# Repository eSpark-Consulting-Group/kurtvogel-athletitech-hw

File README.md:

# Athletitech Product Hardware Development and Enhancements
#### Client Name: Kurt Vogel

## Project Requirements
Outlined in Tickets

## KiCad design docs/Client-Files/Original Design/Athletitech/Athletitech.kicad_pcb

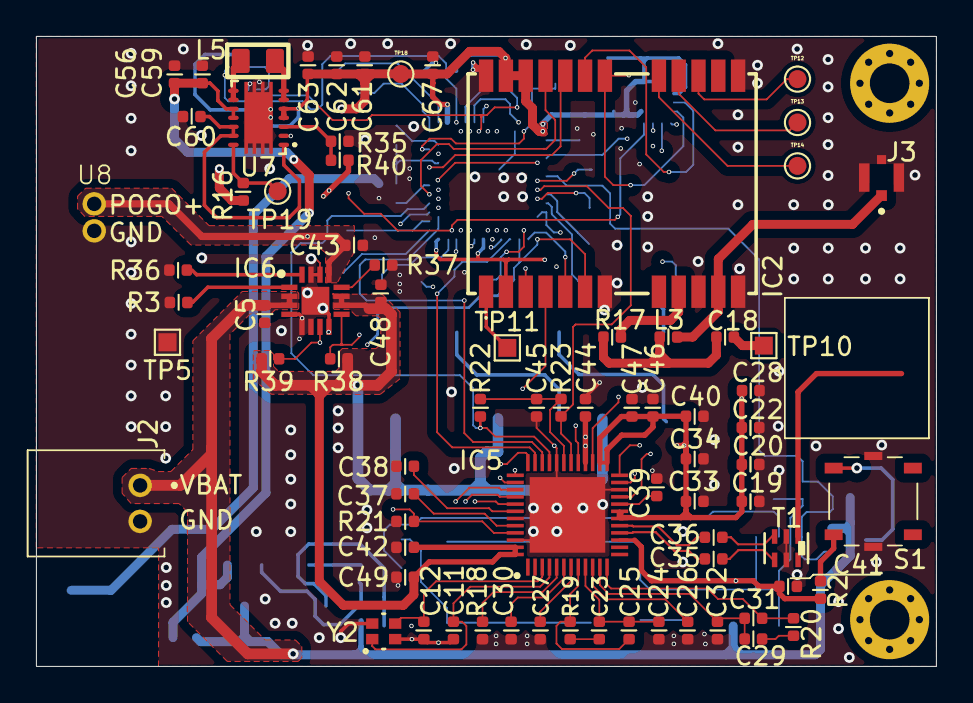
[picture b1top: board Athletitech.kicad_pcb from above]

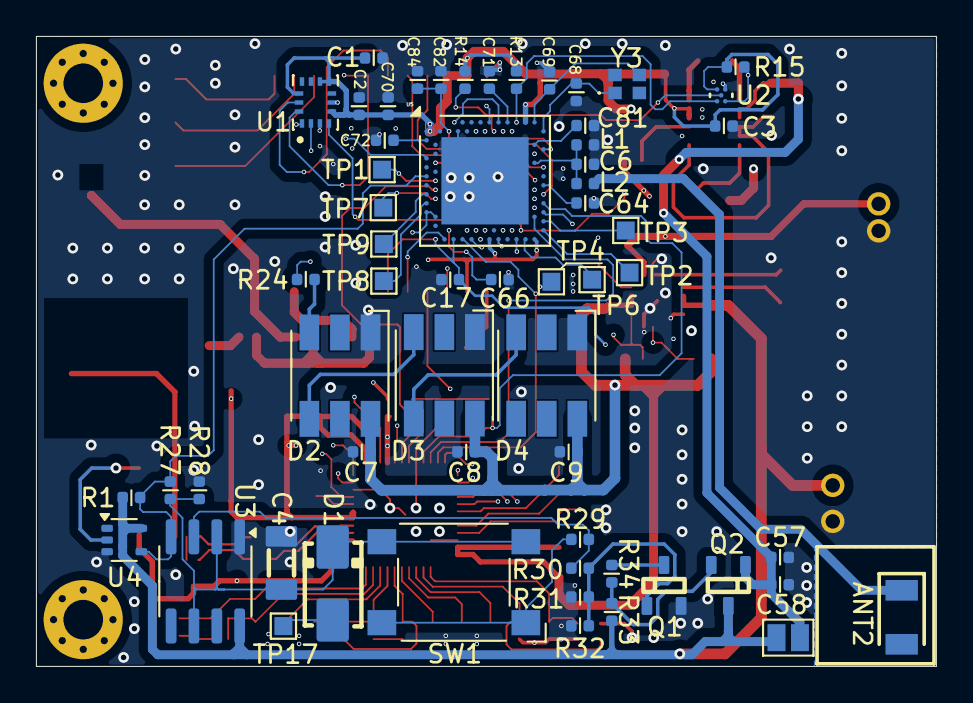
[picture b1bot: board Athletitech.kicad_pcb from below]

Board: 4 copper layers, 50.0 x 35.0 mm, 139 parts (60 on the bottom side), 102 nets.

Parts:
ANT2: 2450AT18B100E; ANTC3216X140N
C1, C2, C3, C27, C30, C43, C60, C72: 100nF; C_0402_1005Metric
C4: 1uF; C_1206
C5, C48: 470nF; C_0402_1005Metric
C6: 1.2pF; C_0402_1005Metric
C7, C8, C9: 0.1uF; C_0402_1005Metric
C11, C12: 10pF; C_0402_1005Metric
C17, C66: 4.7uF; C_0402_1005Metric
C18, C20, C24, C26, C32, C33, C37, C38, C39, C42, C44, C45, C46, C47, C49, C67: 100nf; C_0402_1005Metric
C19: 47uf; C_0402_1005Metric
C22, C34: 10pf; C_0402_1005Metric
C23: 27pf; C_0402_1005Metric
C25: 1P2; C_0402_1005Metric
C28, C40: 330pf; C_0402_1005Metric
C29: 820pf; C_0402_1005Metric
C31: 18pf; C_0402_1005Metric
C35, C36, C68, C69: 12pf; C_0402_1005Metric
C41: 10000pf; C_0402_1005Metric
C56, C59: 10uF; C_0402_1005Metric
C57: 10uF/25V; C_0402_1005Metric
C58: 0.1uF/25V; C_0402_1005Metric
C61, C62, C63: 22uf; C_0402_1005Metric
C64: 820pF; C_0402_1005Metric
C70, C84: 1uF; C_0402_1005Metric
C71, C82: 5pF; C_0402_1005Metric
C81: 100pf; C_0402_1005Metric
D1: B120-E3/61t; D_SMA
D2, D3, D4: SMD-LX5050RGB-TR; LED_RGB_5050-6
H1, H2: MountingHole_Pad; MountingHole_2.2mm_M2_Pad_Via
IC2: NEO-M9N-00B; NEOM9N00B
IC5: DW1000-I-TR13; QFN40P600X600X90-49N-D
IC6: BQ24075RGTT; QFN50P300X300X80-17N-D
J2: S2B-PH-K-S; S2BPHKS
J3: CONMHF4-SMD-G-T; LINX_CONMHF4-SMD-G-T
JP1: Jumper_2_Open; SolderJumper-2_P1.3mm_Open_Pad1.0x1.5mm
L1: 2.7nH; L_0402_1005Metric
L2: 3.3nH; L_0402_1005Metric
L3: 27nH; C_0402_1005Metric
L5: 1.5uH; L_0805
Q1: FDN337N; SOT23-3
Q2: NTR4101PT1G; SOT23-3
R1: 1k; C_0402_1005Metric
R2: 1K; C_0402_1005Metric
R3: 10kΩ; C_0402_1005Metric
R13, R14: 4k7; C_0402_1005Metric
R15: 1k2; C_0402_1005Metric
R16, R40: 1M; C_0402_1005Metric
R17: 10Ω; C_0402_1005Metric
R18: 11K; C_0402_1005Metric
R19: 16K; C_0402_1005Metric
R20: 270; C_0402_1005Metric
R21, R29, R32, R33: 100K; C_0402_1005Metric
R22, R23, R27, R28, R34: 10K; C_0402_1005Metric
R24: 330R; C_0402_1005Metric
R30: 220; C_0402_1005Metric
R31: DNP; C_0402_1005Metric
R35: 180K; C_0402_1005Metric
R36: 1.13kΩ; C_0402_1005Metric
R37: 1.18kΩ; C_0402_1005Metric
R38, R39: 100kΩ; C_0402_1005Metric
S1: EVQ-PT5A15; EVQPT5A15
SG-WFWLB1: TLV493DA2BWXTMA1; SG-WFWLB-5-2
SW1: SW_Omron_B3FS; SW_SPST_Omron_B3FS-100xP
T1: HHM1595A1; HHM-6_2P0X1P25
TP1, TP2, TP3, TP4, TP5, TP6, TP7, TP8, TP9, TP10, TP11, TP17: TestPoint; TestPoint_Pad_1.0x1.0mm
TP12, TP13, TP14, TP18: TestPoint; TestPoint_Pad_D1.0mm
TP19: Power Good; TestPoint_Pad_D1.0mm
U1: ICM-45686; IC_ICM-45686
U3: TLC555IDR; SOIC-8_3.9x4.9mm_P1.27mm
U4: 74AUP1G06, DNP; SOT-353_SC-70-5
U5: nRF52840; Nordic_AQFN-73-1EP_7x7mm_P0.5mm
U7: TPS63020; QFN14-3X4MM
U8: Mill_Max_854-22-002-20-041101
Y2: 8Y38472012; 8Y384_TXC
Y3: XRCGB32M000F1S1DR0; XRCGB

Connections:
+3.3V: C1.1, C2.1, C3.1, C7.1, C8.1, C9.1, C19.2, C20.1, C22.2, C28.2, C33.1, C34.2, C40.2, C41.2, C42.1, C44.1, C46.1, C47.1, C48.1, C49.1, C61.1, C62.1, C63.1, C67.1, C70.1, D2.6 (VDD), D3.6 (VDD), D4.6 (VDD), IC2.2 (D_SEL), IC2.22 (V_BCKP), IC2.23 (VCC), IC5.15 (VDDLNA), IC5.18 (VDDPA1), IC5.19 (VDDPA2), IC5.25 (VDDAON), IC5.26 (VDDLDOD), IC5.28 (VDDIOA), IC5.47 (VDDBATT), IC5.48 (VDDLDOA), IC6.10 (OUT_1), IC6.11 (OUT_2), R2.1, R13.1, R14.1, R15.1, R16.1, R38.1, R39.1, R40.2, SG-WFWLB1.C3 (VDD), TP18.1, U1.5 (VDDIO), U1.8 (VDD), U1.9 (INT2/FSYNC/CLKIN), U1.12 (AP_CS), U5.A22 (VDD), U5.AD14 (VDD), U5.AD23 (VDD), U5.B1 (VDD), U5.W1 (VDD), U5.Y2 (VDDH), U7.4 (VOUT), U7.5 (VOUT_2)
/BAT_OUT: C56.2, C57.1, C58.1, C59.2, JP1.2 (B), Q2.1 (D), U7.10 (VIN), U7.11 (VIN_2)
/Charger - BQ24075/BAT_STATUS_READ: IC6.7 (~PGOOD), R39.2, U5.H2 (P0.27)
/Charger - BQ24075/BAT_nRF: IC6.9 (~CHG), R38.2, U5.V23 (P1.03)
/GNSS - NEO-M9N-00B/EXTINT0: IC2.4 (EXTINT), U5.AC11 (P0.16)
/GNSS - NEO-M9N-00B/PPS: IC2.3 (TIMEPULSE), U5.B13 (AIN1/P0.03)
/GNSS - NEO-M9N-00B/RXD_SPIMOSI: IC2.21 (RXD_/_SPI_MOSI), U5.R24 (P1.06)
/GNSS - NEO-M9N-00B/TXD_SPIMISO: IC2.20 (TXD_/_SPI_MISO), U5.J24 (NFC2/P0.10)
/GNSS - NEO-M9N-00B/USB_D-: IC2.5 (USB_DM), U5.AD4 (D-)
/IMU - ICM-45686/INT1/INT: R15.2, SG-WFWLB1.A1 (/INT), U1.4 (INT1/INT), U5.AC21 (P0.25)
/IMU - ICM-45686/MAS_CLK: U1.3 (RESV/AUX1_SCLK/MAS_CLK), U5.G1 (P0.26)
/IMU - ICM-45686/MAS_DA: U1.2 (RESV/AUX1_SDIO/AUX1_SDI/MAS_DA), U5.A14 (P1.15)
/IMU - ICM-45686/SDO: U1.1 (AP_SDO/AP_AD0), U5.B17 (P1.12)
/MCU - NRF52840-CKAA-R7/DEC1: C72.1, U5.C1 (DEC1)
/MCU - NRF52840-CKAA-R7/DEC3: C81.2, U5.D23 (DEC3)
/MCU - NRF52840-CKAA-R7/DEC4_6: C82.2, C84.2, U5.B5 (DEC4), U5.E24 (DEC6)
/MCU - NRF52840-CKAA-R7/EXTON: IC5.21 (EXTON), U5.AC19 (P0.23)
/MCU - NRF52840-CKAA-R7/GPIO0: IC5.38 (GPIO0/RXOKLED), U5.B19 (P1.11)
/MCU - NRF52840-CKAA-R7/GPIO1: IC5.37 (GPIO1/SFDLED), U5.A16 (P1.13)
/MCU - NRF52840-CKAA-R7/GPIO2: IC5.36 (GPIO2/RXLED), U5.AD10 (P0.15)
/MCU - NRF52840-CKAA-R7/GPIO3: IC5.35 (GPIO3/TXLED), U5.AD8 (P0.13)
/MCU - NRF52840-CKAA-R7/GPIO4: IC5.34 (GPIO4/EXTPA), U5.Y23 (P1.01)
/MCU - NRF52840-CKAA-R7/IRQ: IC5.45 (IRQ/GPIO8), R21.1, U5.P23 (P1.07)
/MCU - NRF52840-CKAA-R7/LED_DIN: R24.1, U5.B11 (AIN4/P0.28)
/MCU - NRF52840-CKAA-R7/P0.07_TRACECLK: TP1.1, U5.M2 (TRACECLK/P0.07)
/MCU - NRF52840-CKAA-R7/P0.11_TRACEDATA2: TP7.1, U5.T2 (TRACEDATA2/P0.11)
/MCU - NRF52840-CKAA-R7/P0.12_TRACEDATA1: TP8.1, U5.U1 (TRACEDATA1/P0.12)
/MCU - NRF52840-CKAA-R7/P1.00_TRACEDATA0: TP6.1, U5.AD22 (TRACEDATA0/P1.00)
/MCU - NRF52840-CKAA-R7/P1.09_TRACEDATA3: TP9.1, U5.R1 (TRACEDATA3/P1.09)
/MCU - NRF52840-CKAA-R7/RESET: TP4.1, U5.AC13 (P0.18/~RESET)
/MCU - NRF52840-CKAA-R7/RSTn: IC5.27 (RSTN), U5.T23 (P1.05)
/MCU - NRF52840-CKAA-R7/SPICLK: IC5.41 (SPICLK), U5.AC9 (P0.14)
/MCU - NRF52840-CKAA-R7/SPICSN: IC5.24 (SPICSN), U5.AC17 (P0.21)
/MCU - NRF52840-CKAA-R7/SPIMISO: IC5.40 (SPIMISO), U5.AD12 (P0.17)
/MCU - NRF52840-CKAA-R7/SPIMOSI: IC5.39 (SPIMOSI), U5.AD16 (P0.20)
/MCU - NRF52840-CKAA-R7/SWDCLK: TP3.1, U5.AA24 (SWDCLK)
/MCU - NRF52840-CKAA-R7/SWDIO: TP2.1, U5.AC24 (SWDIO)
/MCU - NRF52840-CKAA-R7/SYNC: IC5.29 (SYNC/GPIO7), U5.W24 (P1.02)
/MCU - NRF52840-CKAA-R7/WAKEUP: IC5.23 (WAKEUP), U5.AD20 (P0.24)
/MCU - NRF52840-CKAA-R7/XC1: C68.1, U5.B24 (XC1), Y3.1 (XTAL_1)
/MCU - NRF52840-CKAA-R7/XC2: C69.1, U5.A23 (XC2), Y3.3 (XTAL_2)
/POGO+: C43.1, C66.1, IC2.6 (USB_DP), IC6.13 (IN), U5.AD2 (VBUS), U5.AD6 (D+), U8.1
/SCL: IC2.19 (SCL_/_SPI_SLK_), R14.2, SG-WFWLB1.B2 (SCL), U1.13 (AP_SCL/AP_SCLK), U5.B15 (P1.14)
/SDA: IC2.18 (SDA_/_SPI_CS_N), R13.2, SG-WFWLB1.A3 (SDA), U1.14 (AP_SDA/AP_SDIO/AP_SDI), U5.A20 (P1.10)
/UWB - DW1000-I-TR13/GPIO5: IC5.33 (GPIO5/EXTTXE/SPIPOL), R22.2, U5.U24 (P1.04)
/UWB - DW1000-I-TR13/GPIO6: IC5.30 (GPIO6/EXTRXE/SPIPHA), R23.2, U5.P2 (P1.08)
/UWB - DW1000-I-TR13/N: C36.1, T1.3 (BALANCED_PORT_1)
/UWB - DW1000-I-TR13/P: C35.1, T1.4 (BALANCED_PORT_2)
/UWB - DW1000-I-TR13/RF_N: C36.2, IC5.17 (RF_N)
/UWB - DW1000-I-TR13/RF_P: C35.2, IC5.16 (RF_P)
/UWB - DW1000-I-TR13/XTAL1: C12.2, IC5.3 (EXTCLK/XTAL_1), Y2.3 (CRYSTAL_2)
/VBAT: C5.1, IC6.2 (BAT_1), IC6.3 (BAT_2), J2.1, JP1.1 (A), Q2.3 (S), R1.2, R33.2, U3.8 (VCC), U4.5 (VCC)
GND: C1.2, C2.2, C3.2, C4.2, C5.2, C6.1, C7.2, C8.2, C9.2, C11.2, C12.1, C17.2, C19.1, C20.2, C22.1, C24.2, C26.1, C27.2, C28.1, C30.2, C32.2, C33.2, C34.1, C37.2, C38.2, C39.2, C40.1, C41.1, C42.2, C43.2, C44.2, C45.2, C46.2, C47.2, C48.2, C49.2, C56.1, C57.2, C58.2, C59.1, C60.1, C61.2, C62.2, C63.2, C64.1, C66.2, C67.2, C68.2, C69.2, C70.2, C71.2, C72.2, C81.1, C82.1, C84.1, D2.1 (VSS), D3.1 (VSS), D4.1 (VSS), IC2.7 (V_USB), IC2.10 (GND_1), IC2.12 (GND_2), IC2.13 (GND_3), IC2.24 (GND_4), IC5.22 (FORCEON), IC5.32 (VSSIO_1), IC5.43 (VSSIO_2), IC5.46 (TESTMODE), IC5.49 (GND), IC6.4 (~CE), IC6.5 (EN2), IC6.6 (EN1), IC6.8 (VSS), IC6.14 (TMR), IC6.15 (SYSOFF), IC6.17 (VSS_THERMAL_PAD), J2.2, J3.S1, J3.S2, J3.S3, L1.1, Q1.2 (S), R3.1, R18.2, R21.2, R28.2, R31.2, R32.1, R35.1, R36.2, R37.1, S1.MP1, S1.MP2, SG-WFWLB1.C1 (GND), T1.2 (GND_1), T1.5 (GND_2), TP5.1, U1.6 (GND), U3.1 (GND), U4.3 (GND), U5.B7 (VSS), U5.EP (VSS), U5.F23 (VSS_PA), U7.2 (GND), U7.15 (PGND), U7.16 (PGND1), U7.17 (PGND2), U7.18 (PGND3), U7.19 (PGND4), U7.20 (PGND5), U7.21 (PGND6), U7.22 (PGND7), U7.23 (PGND8), U8.2, Y2.2 (GND_1), Y2.4 (GND_2)
MCU_BT_OFF_1: R1.1, R27.1, U3.4 (R), U4.4, U5.L1 (P0.06)
unnamed: ANT2.1 (FEED), L2.1
unnamed: C18.1, TP10.1
unnamed: C18.2, L3.1, R17.2
unnamed: C23.1, R19.2
unnamed: C29.2, R20.1
unnamed: C4.1, D1.2 (A), R27.2, R28.1, SW1.2, U3.2 (TR), U3.6 (THR)
unnamed: D1.1 (K), TP17.1
unnamed: D2.3 (DIN), R24.2
unnamed: D2.4 (DOUT), D3.3 (DIN)
unnamed: D3.4 (DOUT), D4.3 (DIN)
unnamed: IC2.15 (RESERVED_1), TP12.1
unnamed: IC2.16 (RESERVED_2), TP13.1
unnamed: IC2.17 (RESERVED_3), TP14.1
unnamed: IC2.11 (RF_IN), J3.1, L3.2
unnamed: IC2.1 (SAFEBOOT_N), TP11.1
unnamed: IC2.9 (VCC_RF), R17.1
unnamed: C25.1, IC5.8 (CLKTUNE), R19.1
unnamed: C31.2, IC5.12 (VCOTUNE), R20.2
unnamed: C23.2, C24.1, C25.2, IC5.9 (VDDCLK)
unnamed: C37.1, IC5.44 (VDDDIG)
unnamed: C27.1, IC5.7 (VDDIF)
unnamed: C45.1, IC5.31 (VDDIO_1), R22.1, R23.1
unnamed: C38.1, IC5.42 (VDDIO_2)
unnamed: C30.1, IC5.6 (VDDMS)
unnamed: C39.1, IC5.20 (VDDREG)
unnamed: C26.2, IC5.10 (VDDSYN)
unnamed: C29.1, C31.1, C32.1, IC5.11 (VDDVCO)
unnamed: IC5.5 (VREF), R18.1
unnamed: C11.1, IC5.4 (XTAL2), Y2.1 (CRYSTAL_1)
unnamed: IC6.12 (ILIM), R37.2
unnamed: IC6.16 (ISET), R36.1
unnamed: IC6.1 (TS), R3.2
unnamed: Q1.3 (D), R34.2
unnamed: Q1.1 (G), R30.1, R31.1, R32.2
unnamed: Q2.2 (G), R33.1, R34.1
unnamed: R29.2, SW1.1
unnamed: R2.2, S1.B2 (NO_2)
unnamed: R29.1, R30.2, U3.3 (Q)
unnamed: C6.2, L1.2, L2.2, U5.H23 (ANT)
unnamed: C71.1, U5.A18 (DEC2)
unnamed: C64.2, U5.N24 (DEC5)
unnamed: C17.1, U5.AC5 (DECUSB)
unnamed: C60.2, U7.1 (VINA), U7.12 (EN), U7.13 (PS/SYNC)
unnamed: R35.2, R40.1, U7.3 (FB)
unnamed: L5.1, U7.8 (L1), U7.9 (L1_2)
unnamed: L5.2, U7.6 (L2), U7.7 (L2_2)
unnamed: R16.2, TP19.1, U7.14 (PG)
POWER_OFF: S1.A2 (COM_2), U4.2

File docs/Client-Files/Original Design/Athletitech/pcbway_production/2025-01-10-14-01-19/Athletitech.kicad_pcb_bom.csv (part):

Designator,Quantity,Value,Footprint,Package,MPN,DNP,Mount_Type,MANUFACTURER_NAME,MF,MOUSER_PRICE-STOCK,DESCRIPTION,MOUSER_PART_NUMBER,Price,Check_prices,HEIGHT,MP,SnapEDA_Link,ARROW_PRICE-STOCK,ARROW_PART_NUMBER,Description_1,Availability,MANUFACTURER_PART_NUMBER,Description,Field4,Field5,Field6,Field7,Field8,Part Description,Digikey,LCSC Part #,Manufacturer,Height,Manufacturer_Name,Mouser Part Number,Mouser Price/Stock,Arrow Part Number,Arrow Price/Stock,Purchase-URL,Sim.Device,Sim.Type,Sim.Pins,PARTREV,STANDARD,MAXIMUM_PACKAGE_HEIGHT,MANUFACTURER,MNP
ANT2,1,2450AT18B100E,ANTC3216X140N,None,,,smt,JOHANSON TECHNOLOGY,Johanson,https://www.mouser.co.uk/ProductDetail/Johanson-Technology/2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,Antennas 2.45GHz ANTENNA,609-2450AT18B100E,None,https://www.snapeda.com/parts/2450AT18B100E/AN/view-part/?ref=eda,1.4mm,2450AT18B100E,https://www.snapeda.com/parts/2450AT18B100E/AN/view-part/?ref=snap,https://www.arrow.com/en/products/2450at18b100e/johanson-die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,2450AT18B100E,"
                        
                            Antenna Chip -0.5dBi Gain 2500MHz 2-Pin CSMD T/R
                        
",In Stock,2450AT18B100E,,,,,,,,,,,,,,,,,,,,,,,,,
"C1, C2, C3, C43",4,100nF,C_0402_1005Metric,,,,smt,,,,,,,,,,,,,,,,"Unpolarized capacitor, small symbol",Farnell,2611911,RM EMK105 B7104KV-F,TAIYO YUDEN EUROPE GMBH,110091611,	0.1uF 10% 16V Ceramic Capacitor X7R 0402 (1005 Metric),,,,,,,,,,,,,,,,,,
"C11, C12",2,10pF,C_0402_1005Metric,,04025C222K4T4A,,smt,,,,,,,,,,,,,,,,,Farnell,2611911,RM EMK105 B7104KV-F,TAIYO YUDEN EUROPE GMBH,110091611,	0.1uF 10% 16V Ceramic Capacitor X7R 0402 (1005 Metric),,,,,,,,,,,,,,,,,,
"C17, C66",2,4.7uF,C_0402_1005Metric,,C1005X7R1C104K050BC,,smt,,,,,,,,,,,,,,,,"Unpolarized capacitor, small symbol",Farnell,2611911,RM EMK105 B7104KV-F,TAIYO YUDEN EUROPE GMBH,110091611,	0.1uF 10% 16V Ceramic Capacitor X7R 0402 (1005 Metric),,,,,,,,,,,,,,,,,,
"C18, C67",2,100nf,C_0402_1005Metric,,C1005X7R1C104K050BC,,smt,,,,,,,,,,,,,,,,"Unpolarized capacitor, small symbol",Farnell,2611911,RM EMK105 B7104KV-F,TAIYO YUDEN EUROPE GMBH,110091611,	0.1uF 10% 16V Ceramic Capacitor X7R 0402 (1005 Metric),,,,,,,,,,,,,,,,,,
C19,1,47uf,C_0402_1005Metric,,JMK316ABJ476ML8T,,smt,,,,,,,,,,,,,,,,"Unpolarized capacitor, small symbol",Farnell,2611911,RM EMK105 B7104KV-F,TAIYO YUDEN EUROPE GMBH,110091611,	0.1uF 10% 16V Ceramic Capacitor X7R 0402 (1005 Metric),,,,,,,,,,,,,,,,,,
"C20, C24, C26, C32, C33, C37, C38, C39, C42, C44, C45, C46, C47, C49",14,100nf,C_0402_1005Metric,,TMK105B7104KVHF,,smt,,,,,,,,,,,,,,,,"Unpolarized capacitor, small symbol",Farnell,2611911,RM EMK105 B7104KV-F,TAIYO YUDEN EUROPE GMBH,110091611,	0.1uF 10% 16V Ceramic Capacitor X7R 0402 (1005 Metric),,,,,,,,,,,,,,,,,,
"C22, C34",2,10pf,C_0402_1005Metric,,KGM05ACG1H100JH,,smt,,,,,,,,,,,,,,,,"Unpolarized capacitor, small symbol",Farnell,2611911,RM EMK105 B7104KV-F,TAIYO YUDEN EUROPE GMBH,110091611,	0.1uF 10% 16V Ceramic Capacitor X7R 0402 (1005 Metric),,,,,,,,,,,,,,,,,,
C23,1,27pf,C_0402_1005Metric,,VJ0402A270JXQPW1BC,,smt,,,,,,,,,,,,,,,,"Unpolarized capacitor, small symbol",Farnell,2611911,RM EMK105 B7104KV-F,TAIYO YUDEN EUROPE GMBH,110091611,	0.1uF 10% 16V Ceramic Capacitor X7R 0402 (1005 Metric),,,,,,,,,,,,,,,,,,
C25,1,1P2,C_0402_1005Metric,,GRM0225C1H1R2CA03L,,smt,,,,,,,,,,,,,,,,"Unpolarized capacitor, small symbol",Farnell,2611911,RM EMK105 B7104KV-F,TAIYO YUDEN EUROPE GMBH,110091611,	0.1uF 10% 16V Ceramic Capacitor X7R 0402 (1005 Metric),,,,,,,,,,,,,,,,,,
"C27, C30, C60",3,100nF,C_0402_1005Metric,,CL10B104KA8WPNC,,smt,,,,,,,,,,,,,,,,"Unpolarized capacitor, small symbol",Farnell,2611911,RM EMK105 B7104KV-F,TAIYO YUDEN EUROPE GMBH,110091611,	0.1uF 10% 16V Ceramic Capacitor X7R 0402 (1005 Metric),,,,,,,,,,,,,,,,,,
"C28, C40",2,330pf,C_0402_1005Metric,,MAASU105SB7331KFCA01,,smt,,,,,,,,,,,,,,,,"Unpolarized capacitor, small symbol",Farnell,2611911,RM EMK105 B7104KV-F,TAIYO YUDEN EUROPE GMBH,110091611,	0.1uF 10% 16V Ceramic Capacitor X7R 0402 (1005 Metric),,,,,,,,,,,,,,,,,,
C29,1,820pf,C_0402_1005Metric,,UMK105B7821KV-F,,smt,,,,,,,,,,,,,,,,"Unpolarized capacitor, small symbol",Farnell,2611911,RM EMK105 B7104KV-F,TAIYO YUDEN EUROPE GMBH,110091611,	0.1uF 10% 16V Ceramic Capacitor X7R 0402 (1005 Metric),,,,,,,,,,,,,,,,,,
C31,1,18pf,C_0402_1005Metric,,VJ0402A180KXQCW1BC,,smt,,,,,,,,,,,,,,,,"Unpolarized capacitor, small symbol",Farnell,2611911,RM EMK105 B7104KV-F,TAIYO YUDEN EUROPE GMBH,110091611,	0.1uF 10% 16V Ceramic Capacitor X7R 0402 (1005 Metric),,,,,,,,,,,,,,,,,,
"C35, C36, C68, C69",4,12pf,C_0402_1005Metric,,CBR04C120J5GACAUTO,,smt,,,,,,,,,,,,,,,,"Unpolarized capacitor, small symbol",Farnell,2611911,RM EMK105 B7104KV-F,TAIYO YUDEN EUROPE GMBH,110091611,"[C35,C36]	0.1uF 10% 16V Ceramic Capacitor X7R 0402 (1005 Metric); [C68,C69]0.1 µF ±10% 16V Ceramic Capacitor X7R 0402 (1005 Metric)",587-1451-1-ND,C385888,Taiyo Yuden,,,,,,,,,,,,,,,
C4,1,1uF,C_1206,,,,smt,,,,,,,,,,,,,,,,Polarized capacitor,,,,,,,,,,,,,,,,,,,,,,,,
C41,1,10000pf,C_0402_1005Metric,,KAM05AR71E103KH,,smt,,,,,,,,,,,,,,,,"Unpolarized capacitor, small symbol",Farnell,2611911,RM EMK105 B7104KV-F,TAIYO YUDEN EUROPE GMBH,110091611,	0.1uF 10% 16V Ceramic Capacitor X7R 0402 (1005 Metric),,,,,,,,,,,,,,,,,,
"C48, C5",2,470nF,C_0402_1005Metric,,,,smt,,,,,,,,,,,,,,,,"Unpolarized capacitor, small symbol",Farnell,2611911,RM EMK105 B7104KV-F,TAIYO YUDEN EUROPE GMBH,110091611,	0.1uF 10% 16V Ceramic Capacitor X7R 0402 (1005 Metric),,,,,,,,,,,,,,,,,,
"C56, C59",2,10uF,C_0402_1005Metric,,CL10A106MQ8NNNC,,smt,,,,,,,,,,,,,,,,"Unpolarized capacitor, small symbol",Farnell,2611911,RM EMK105 B7104KV-F,TAIYO YUDEN EUROPE GMBH,110091611,	0.1uF 10% 16V Ceramic Capacitor X7R 0402 (1005 Metric),,,,,,,,,,,,,,,,,,
C57,1,10uF/25V,C_0402_1005Metric,,,,smt,,,,,,,,,,,,,,,,"Unpolarized capacitor, small symbol",Farnell,2611911,RM EMK105 B7104KV-F,TAIYO YUDEN EUROPE GMBH,110091611,	0.1uF 10% 16V Ceramic Capacitor X7R 0402 (1005 Metric),,,,,,,,,,,,,,,,,,
C58,1,0.1uF/25V,C_0402_1005Metric,,CL10B104KA8NFNC,,smt,,,,,,,,,,,,,,,,"Unpolarized capacitor, small symbol",Farnell,2611911,RM EMK105 B7104KV-F,TAIYO YUDEN EUROPE GMBH,110091611,	0.1uF 10% 16V Ceramic Capacitor X7R 0402 (1005 Metric),,,,,,,,,,,,,,,,,,
C6,1,1.2pF,C_0402_1005Metric,,CC0402DRNPO9BN5R0,,smt,,,,,,,,,,,,,,,,"Unpolarized capacitor, small symbol",Farnell,2611911,RM EMK105 B7104KV-F,TAIYO YUDEN EUROPE GMBH,110091611,0.1 µF ±10% 16V Ceramic Capacitor X7R 0402 (1005 Metric),587-1451-1-ND,C385888,Taiyo Yuden,,,,,,,,,,,,,,,
"C61, C62, C63",3,22uf,C_0402_1005Metric,,LMK212BBJ226MG-T,,smt,,,,,,,,,,,,,,,,"Unpolarized capacitor, small symbol",Farnell,2611911,RM EMK105 B7104KV-F,TAIYO YUDEN EUROPE GMBH,110091611,	0.1uF 10% 16V Ceramic Capacitor X7R 0402 (1005 Metric),,,,,,,,,,,,,,,,,,
C64,1,820pF,C_0402_1005Metric,,CC0402DRNPO9BN5R0,,smt,,,,,,,,,,,,,,,,"Unpolarized capacitor, small symbol",Farnell,2611911,RM EMK105 B7104KV-F,TAIYO YUDEN EUROPE GMBH,110091611,0.1 µF ±10% 16V Ceramic Capacitor X7R 0402 (1005 Metric),587-1451-1-ND,C385888,Taiyo Yuden,,,,,,,,,,,,,,,
"C7, C8, C9",3,0.1uF,C_0402_1005Metric,,CC0402DRNPO9BN5R0,,smt,,,,,,,,,,,,,,,,"Unpolarized capacitor, small symbol",Farnell,2611911,RM EMK105 B7104KV-F,TAIYO YUDEN EUROPE GMBH,110091611,	0.1uF 10% 16V Ceramic Capacitor X7R 0402 (1005 Metric),,,,,,,,,,,,,,,,,,
C70,1,1uF,C_0402_1005Metric,,CC0402DRNPO9BN5R0,,smt,,,,,,,,,,,,,,,,"Unpolarized capacitor, small symbol",Farnell,2611911,RM EMK105 B7104KV-F,TAIYO YUDEN EUROPE GMBH,110091611,	0.1uF 10% 16V Ceramic Capacitor X7R 0402 (1005 Metric),,,,,,,,,,,,,,,,,,
"C71, C82",2,NC,C_0402_1005Metric,,CC0402DRNPO9BN5R0,,smt,,,,,,,,,,,,,,,,"Unpolarized capacitor, small symbol",Farnell,2611911,RM EMK105 B7104KV-F,TAIYO YUDEN EUROPE GMBH,110091611,0.1 µF ±10% 16V Ceramic Capacitor X7R 0402 (1005 Metric),587-1451-1-ND,C385888,Taiyo Yuden,,,,,,,,,,,,,,,
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
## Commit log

2025-03-27 Add: client original design
2025-04-07 #3 initial commit Added client files in unzip format
2025-04-07 #3 Updated power and charger sheet (in progress )
2025-04-08 #3 Updated schematic (power, charger,GPS,IMU,MagneticSensor,MCU,UWB) sheets (in progress)
2025-04-09 #3 Updated Power,GPS,IMU,MCU,UWB,MAGNETO sheets
2025-04-10 #3 updated schematic design
2025-04-10 #3 updated Schematic design (replaced power latch IC with analog switch based scheme) Done
2025-04-14 #4 (minor schematic changes done ) Component placement updated
2025-04-15 #4 Updated boost converter, Power sheet, Updated PCB component placement(in progress)
2025-04-16 #4 Updated PCB design (in progress)
2025-04-17 #4 updated component placement (in progress)
2025-04-18 #3 updated capacitor footprint, component placement updated
2025-04-28 #5 updated schematic design
